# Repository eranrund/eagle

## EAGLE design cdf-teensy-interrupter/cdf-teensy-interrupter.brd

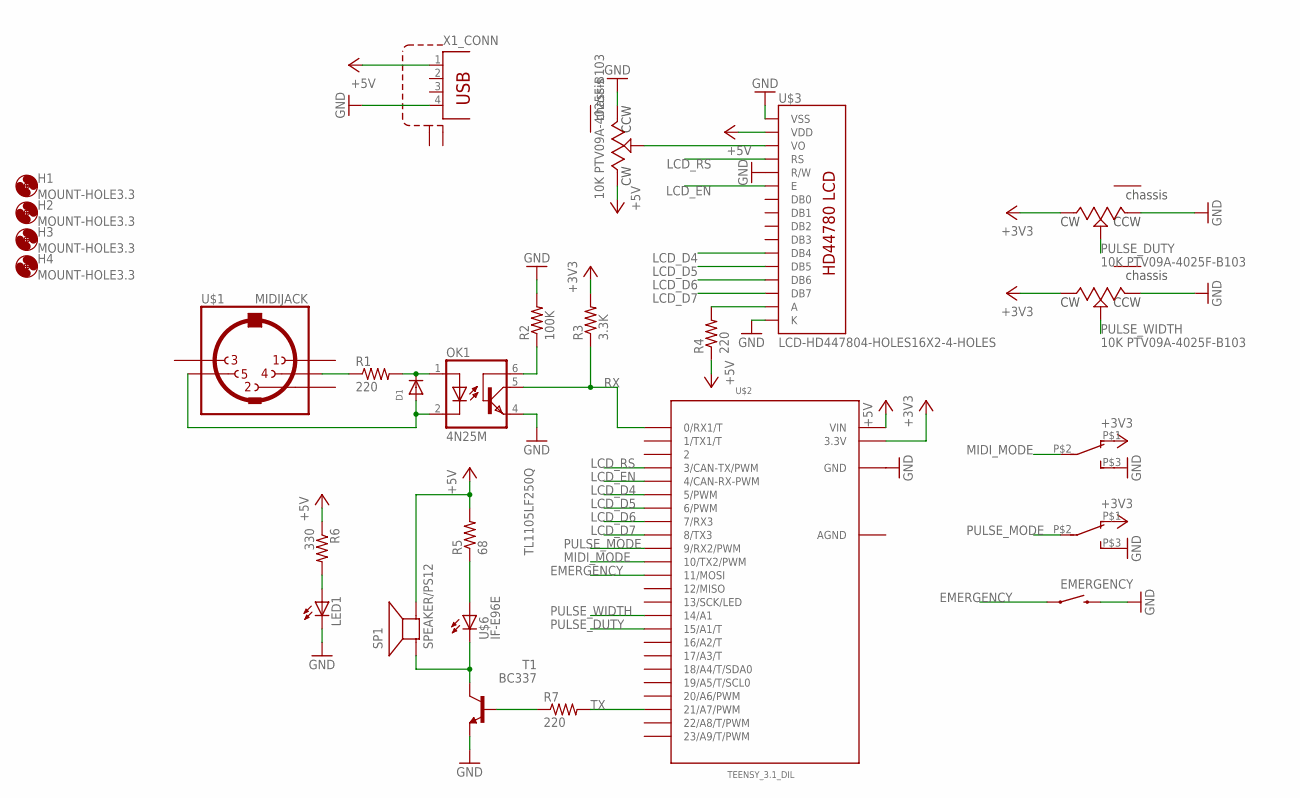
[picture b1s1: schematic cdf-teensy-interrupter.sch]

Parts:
D1: DIODEDO-1N4148; DO-1N4148
EMERGENCY: SWITCH-MOMENTARY-2PTH; TACTILE-PTH
H1, H2, H3, H4: MOUNT-HOLE3.3; 3,3
LCD_BL: 10K PTV09A-4025F-B103; PTV09A-4
LED1: LED5MM
MIDI_MODE: 100SP1T1B4M2QE
OK1: 4N25M; DIL06
PULSE_DUTY: 10K PTV09A-4025F-B103; PTV09A-4
PULSE_MODE: 100SP1T1B4M2QE
PULSE_WIDTH: 10K PTV09A-4025F-B103; PTV09A-4
R1, R4, R7: 220; 0204/7
R2: 100K; 0204/7
R3: 3.3K; 0204/7
R5: 68; 0204/7
R6: 330; 0204/7
SP1: SPEAKER/PS12; PS12
T1: BC337; TO92
U$1: MIDIJACK; CP-2350
U$2: TEENSY_3.1_DIL; TEENSY3-DIL
U$3: LCD-HD447804-HOLES16X2-4-HOLES; LCD-16X2-4HOLES
U$6: IF-E96E
X1: TE-292304-1

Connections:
+3V3: MIDI_MODE.P$1 (1), PULSE_DUTY.3 (CW), PULSE_MODE.P$1 (1), PULSE_WIDTH.3 (CW), R3.2, U$2.3.3V
+5V: LCD_BL.3 (CW), R4.1, R5.2, R6.1, SP1.P$2 (-), U$2.VIN, U$3.2 (VDD), X1.1
AGND: U$2.AGND
EMERGENCY: EMERGENCY.1, U$2.11 (11/MOSI)
GND: EMERGENCY.3 (2), LCD_BL.1 (CCW), LED1.K (C), MIDI_MODE.P$3 (3), OK1.4 (EMI), PULSE_DUTY.1 (CCW), PULSE_MODE.P$3 (3), PULSE_WIDTH.1 (CCW), R2.2, T1.1 (E), U$2.GND, U$3.1 (VSS), U$3.5 (R/W), U$3.16 (K), X1.4
LCD_D4: U$2.5 (5/PWM), U$3.11 (DB4)
LCD_D5: U$2.6 (6/PWM), U$3.12 (DB5)
LCD_D6: U$2.7 (7/RX3), U$3.13 (DB6)
LCD_D7: U$2.8 (8/TX3), U$3.14 (DB7)
LCD_EN: U$2.4 (4/CAN-RX-PWM), U$3.6 (E)
LCD_RS: U$2.3 (3/CAN-TX/PWM), U$3.4 (RS)
MIDI_MODE: MIDI_MODE.P$2 (2), U$2.10 (10/TX2/PWM)
unnamed: R1.1, U$1.4
unnamed: D1.C, OK1.1 (A), R1.2
unnamed: D1.A, OK1.2 (C), U$1.5
unnamed: OK1.6 (BAS), R2.1
unnamed: LCD_BL.2 (WIPER), U$3.3 (VO)
unnamed: R4.2, U$3.15 (A)
unnamed: R7.1, T1.2 (B)
unnamed: R5.1, U$6.P$2_ANODE+ (A)
unnamed: LED1.A, R6.2
unnamed: SP1.P$1 (+), T1.3 (C), U$6.P$1_CATHODE- (C)
PULSE_DUTY: PULSE_DUTY.2 (WIPER), U$2.15/A1 (15/A1/T)
PULSE_MODE: PULSE_MODE.P$2 (2), U$2.9 (9/RX2/PWM)
PULSE_WIDTH: PULSE_WIDTH.2 (WIPER), U$2.14/A0 (14/A1)
RX: OK1.5 (COL), R3.1, U$2.0 (0/RX1/T)
TX: R7.2, U$2.21/A7 (21/A7/PWM)

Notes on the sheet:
TL1105LF250Q

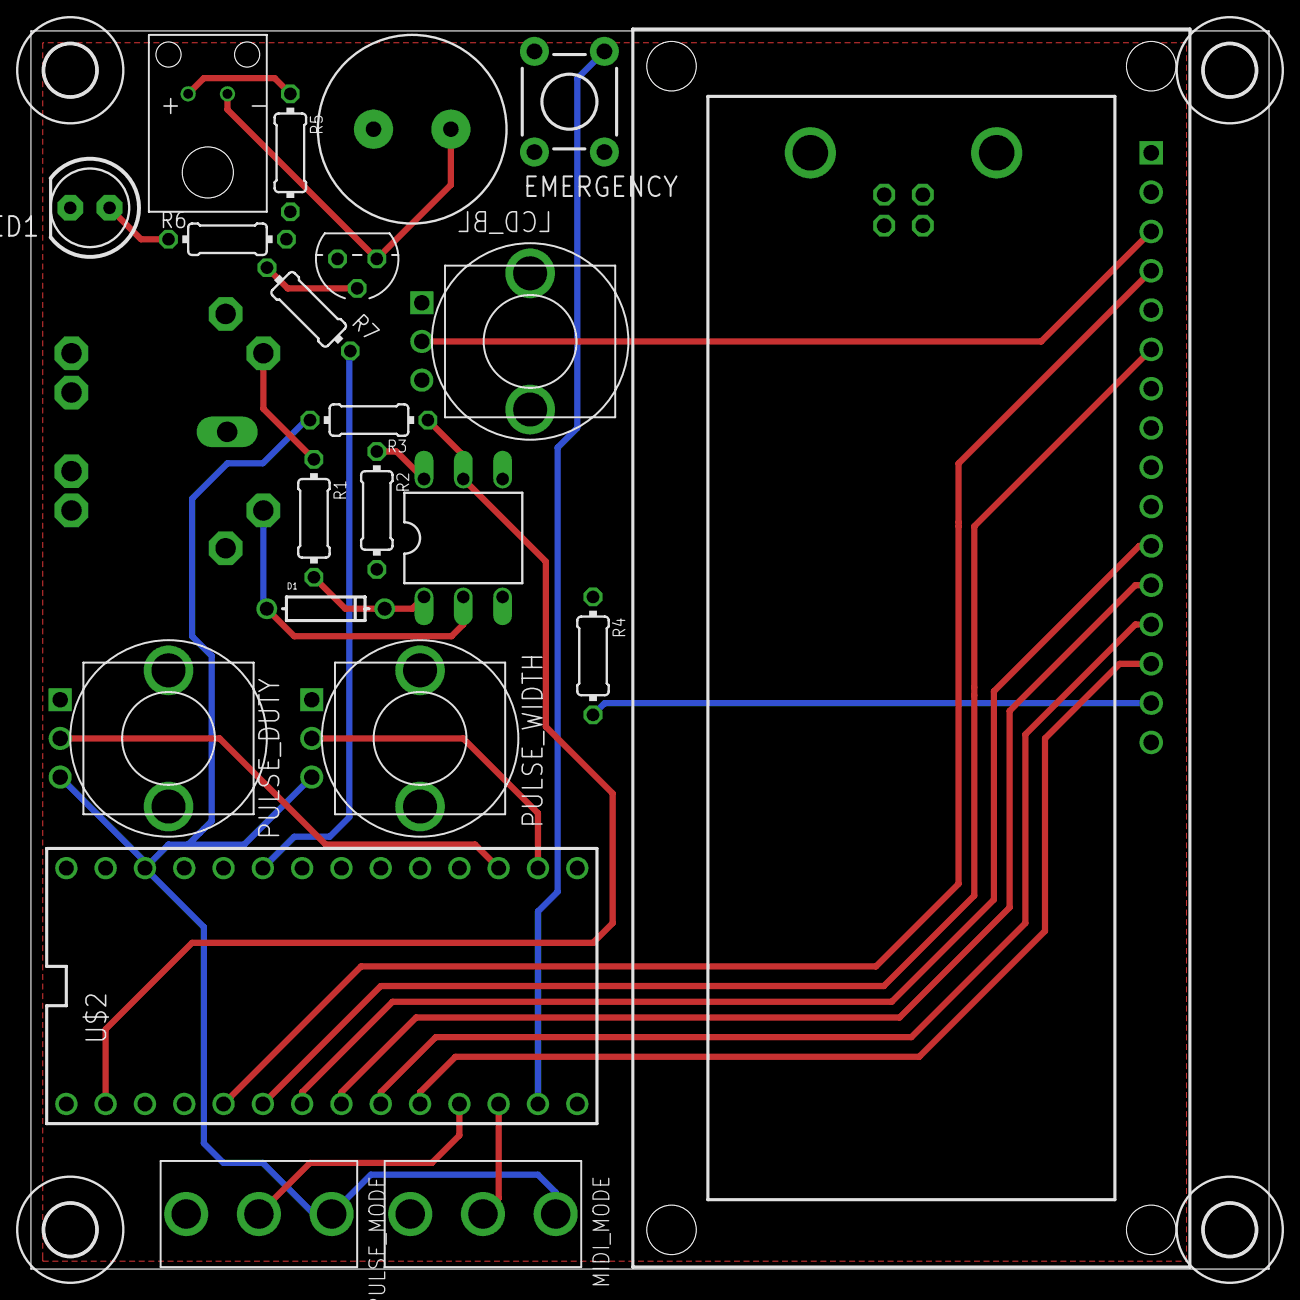
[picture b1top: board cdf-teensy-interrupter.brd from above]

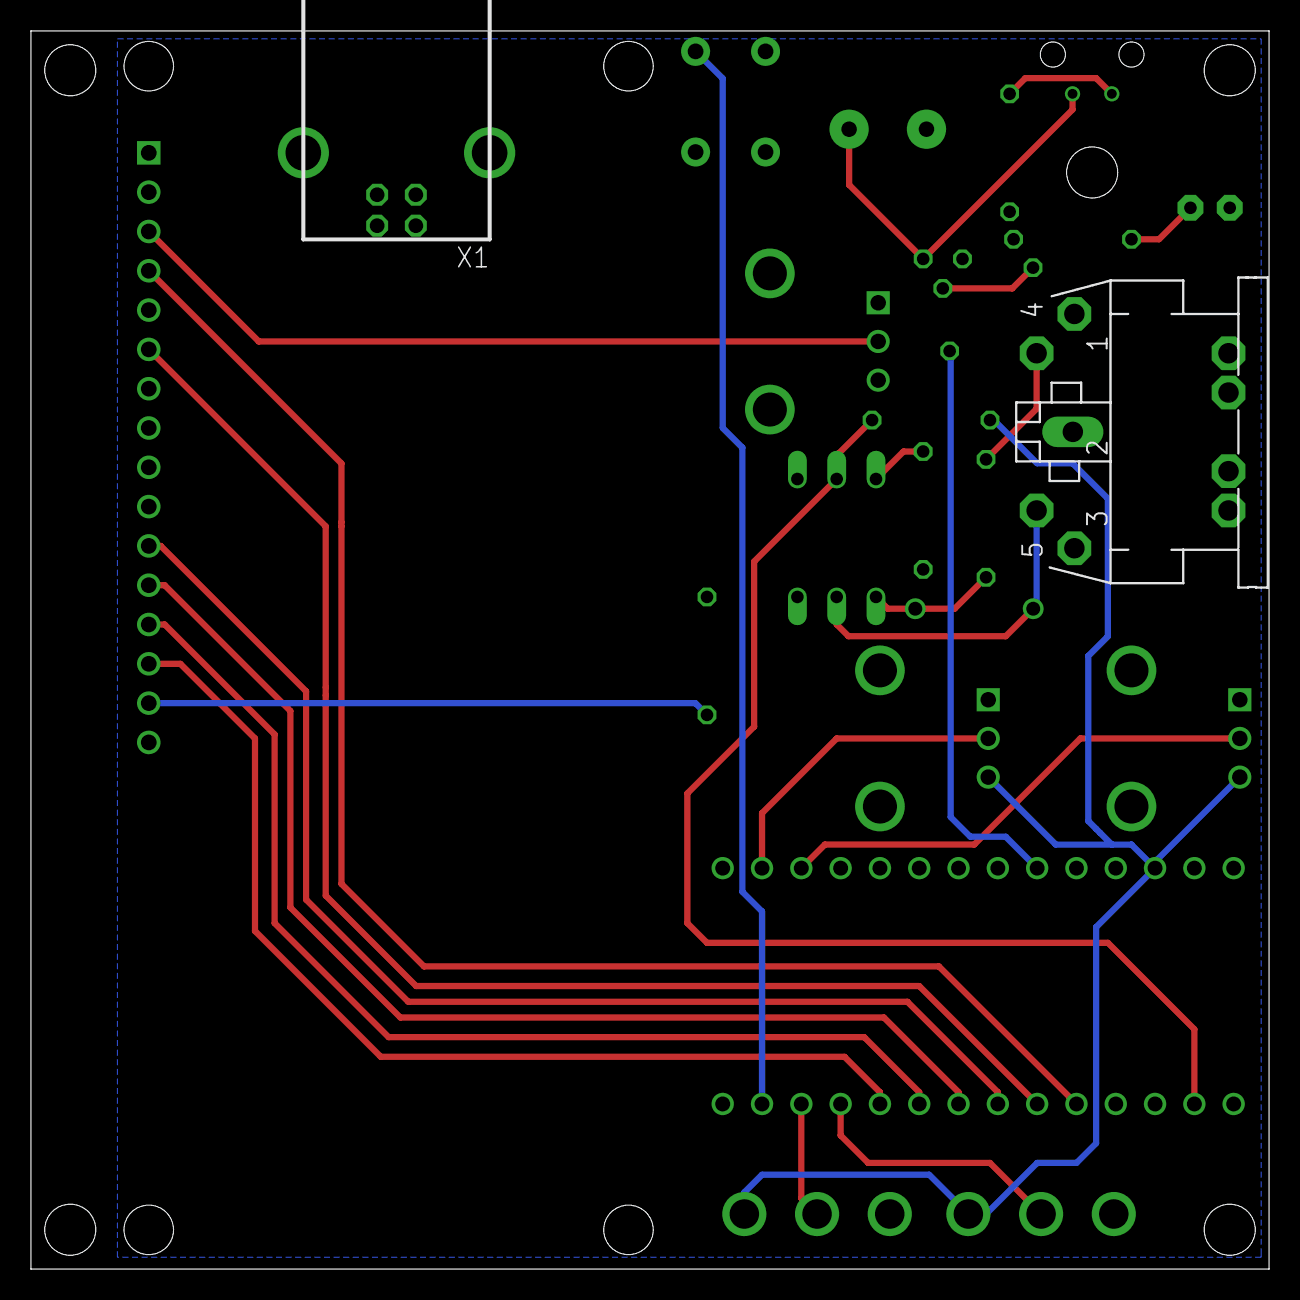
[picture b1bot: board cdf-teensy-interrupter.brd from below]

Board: 2 copper layers, 80.0 x 80.0 mm, 27 parts (2 on the bottom side), 26 nets.

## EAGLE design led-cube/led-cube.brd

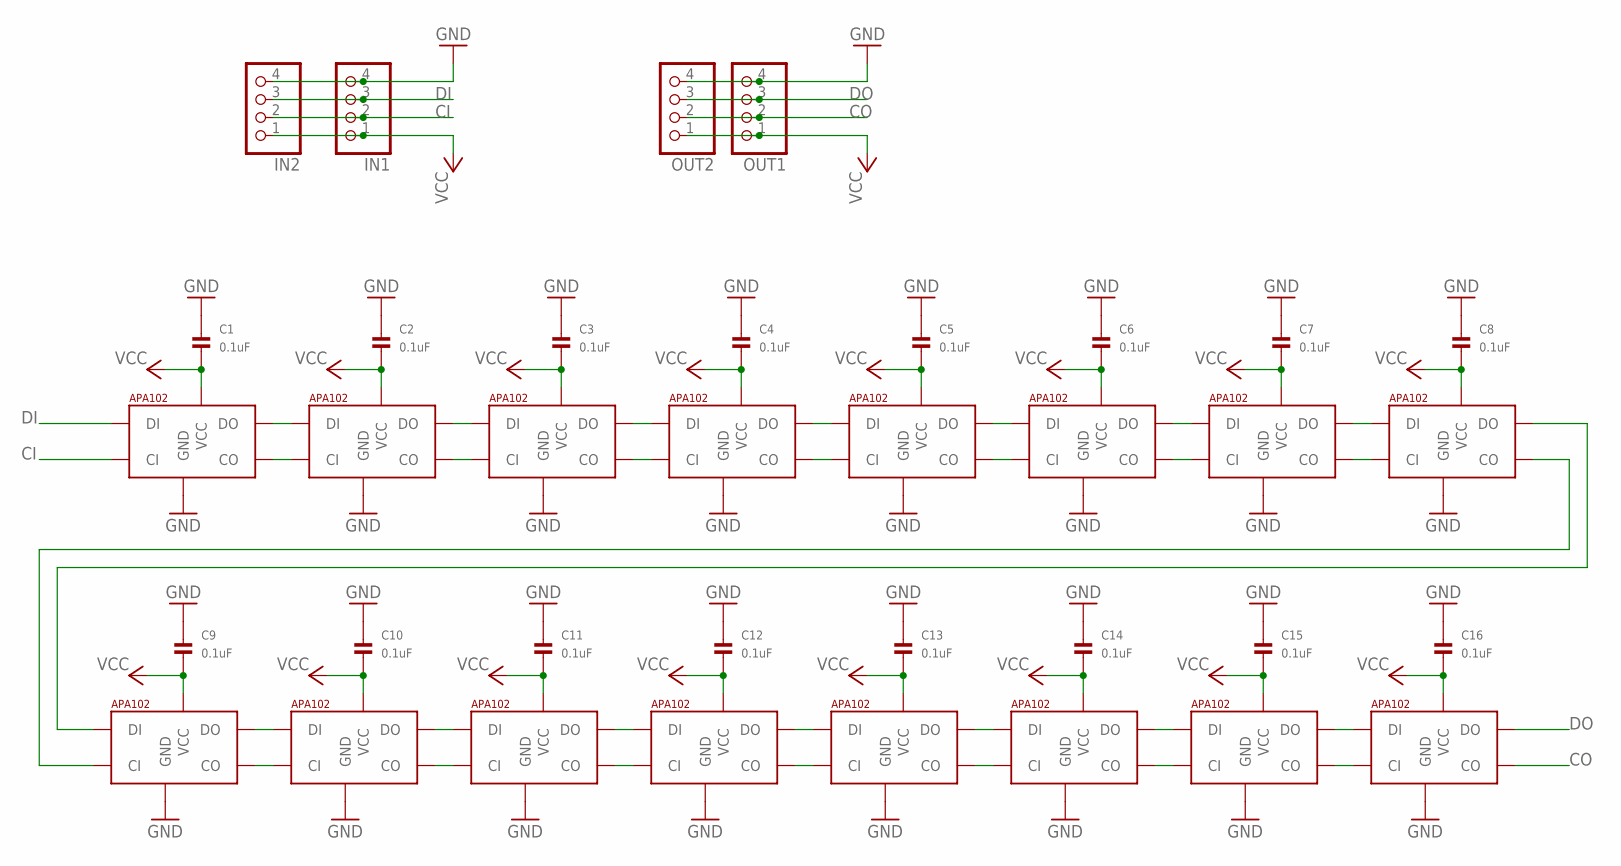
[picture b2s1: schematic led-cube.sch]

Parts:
C1, C2, C3, C4, C5, C6, C7, C8, C9, C10, C11, C12, C13, C14, C15, C16: 0.1uF; 0603
IN1, IN2: PINHD-1X4; 1X04
OUT1, OUT2: PINHD-1X4; 1X04
U$1, U$2, U$3, U$4, U$5, U$6, U$7, U$8, U$9, U$10, U$11, U$12, U$13, U$14, U$15, U$16: APA1025050; APA102_5050

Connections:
CI: IN1.2, IN2.2, U$1.5 (CI)
CO: OUT1.2, OUT2.2, U$16.2 (CO)
DI: IN1.3, IN2.3, U$1.4 (DI)
DO: OUT1.3, OUT2.3, U$16.3 (DO)
GND: C1.1, C2.1, C3.1, C4.1, C5.1, C6.1, C7.1, C8.1, C9.1, C10.1, C11.1, C12.1, C13.1, C14.1, C15.1, C16.1, IN1.4, IN2.4, OUT1.4, OUT2.4, U$1.6 (GND), U$2.6 (GND), U$3.6 (GND), U$4.6 (GND), U$5.6 (GND), U$6.6 (GND), U$7.6 (GND), U$8.6 (GND), U$9.6 (GND), U$10.6 (GND), U$11.6 (GND), U$12.6 (GND), U$13.6 (GND), U$14.6 (GND), U$15.6 (GND), U$16.6 (GND)
unnamed: U$1.2 (CO), U$2.5 (CI)
unnamed: U$1.3 (DO), U$2.4 (DI)
unnamed: U$3.2 (CO), U$4.5 (CI)
unnamed: U$3.3 (DO), U$4.4 (DI)
unnamed: U$2.3 (DO), U$3.4 (DI)
unnamed: U$2.2 (CO), U$3.5 (CI)
unnamed: U$5.2 (CO), U$6.5 (CI)
unnamed: U$5.3 (DO), U$6.4 (DI)
unnamed: U$7.2 (CO), U$8.5 (CI)
unnamed: U$7.3 (DO), U$8.4 (DI)
unnamed: U$6.3 (DO), U$7.4 (DI)
unnamed: U$6.2 (CO), U$7.5 (CI)
unnamed: U$4.3 (DO), U$5.4 (DI)
unnamed: U$4.2 (CO), U$5.5 (CI)
unnamed: U$9.2 (CO), U$10.5 (CI)
unnamed: U$9.3 (DO), U$10.4 (DI)
unnamed: U$11.2 (CO), U$12.5 (CI)
unnamed: U$11.3 (DO), U$12.4 (DI)
unnamed: U$10.3 (DO), U$11.4 (DI)
unnamed: U$10.2 (CO), U$11.5 (CI)
unnamed: U$13.2 (CO), U$14.5 (CI)
unnamed: U$13.3 (DO), U$14.4 (DI)
unnamed: U$15.2 (CO), U$16.5 (CI)
unnamed: U$15.3 (DO), U$16.4 (DI)
unnamed: U$14.3 (DO), U$15.4 (DI)
unnamed: U$14.2 (CO), U$15.5 (CI)
unnamed: U$12.3 (DO), U$13.4 (DI)
unnamed: U$12.2 (CO), U$13.5 (CI)
unnamed: U$8.3 (DO), U$9.4 (DI)
unnamed: U$8.2 (CO), U$9.5 (CI)
VCC: C1.2, C2.2, C3.2, C4.2, C5.2, C6.2, C7.2, C8.2, C9.2, C10.2, C11.2, C12.2, C13.2, C14.2, C15.2, C16.2, IN1.1, IN2.1, OUT1.1, OUT2.1, U$1.1 (VCC), U$2.1 (VCC), U$3.1 (VCC), U$4.1 (VCC), U$5.1 (VCC), U$6.1 (VCC), U$7.1 (VCC), U$8.1 (VCC), U$9.1 (VCC), U$10.1 (VCC), U$11.1 (VCC), U$12.1 (VCC), U$13.1 (VCC), U$14.1 (VCC), U$15.1 (VCC), U$16.1 (VCC)

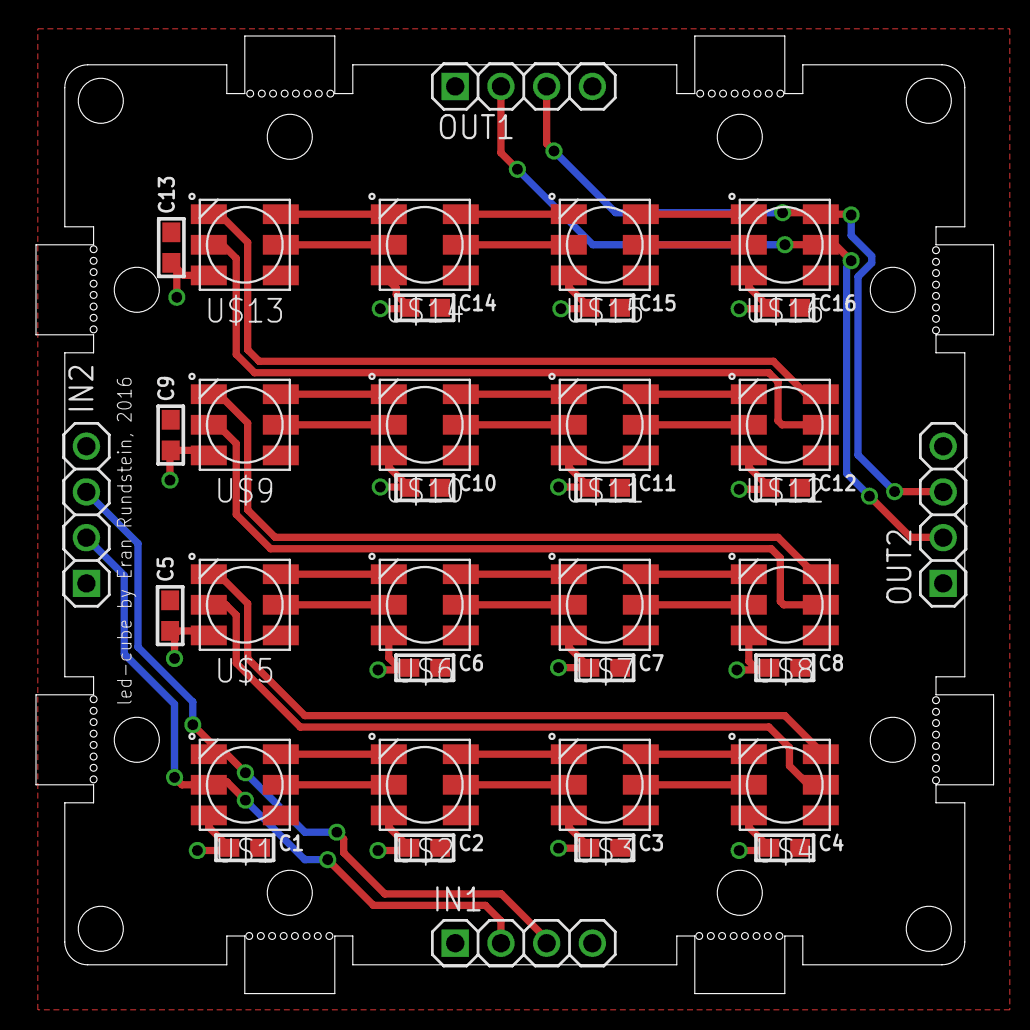
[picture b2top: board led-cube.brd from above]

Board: 2 copper layers, 53.2 x 53.2 mm, 36 parts (0 on the bottom side), 36 nets.

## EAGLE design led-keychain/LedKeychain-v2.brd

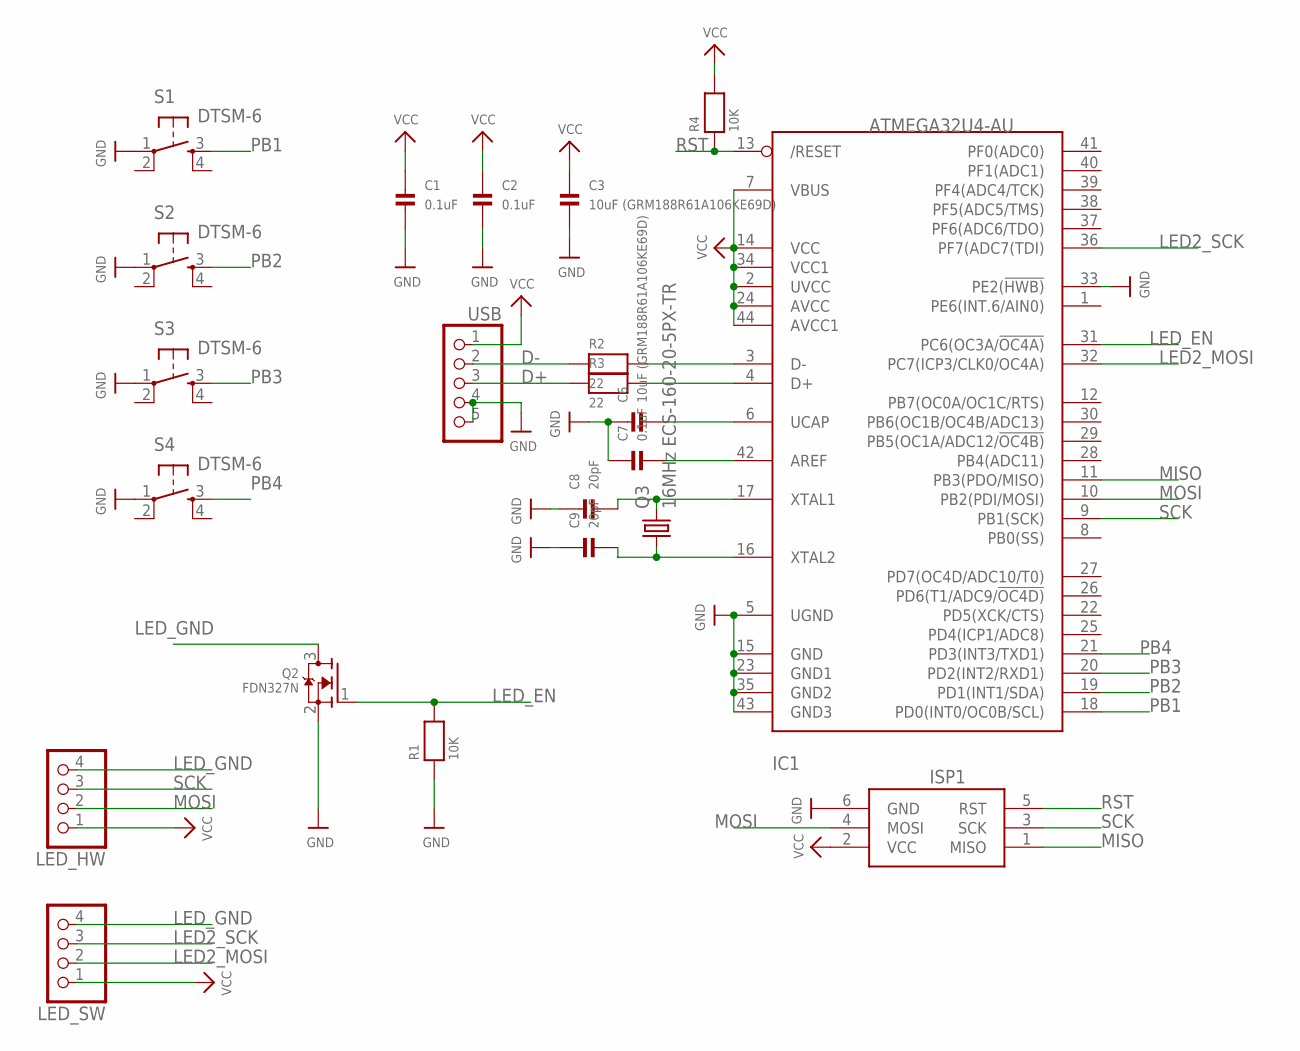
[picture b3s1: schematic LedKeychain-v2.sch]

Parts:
C1, C2, C7: 0.1uF; 0603-MINI
C3, C6: 10uF (GRM188R61A106KE69D); 1206
C8, C9: 20pF; 0603-MINI
IC1: ATMEGA32U4-AU; TQFP44
ISP1: AVRISP-6; AVRISP
LED_HW: HEADER-1X4ROUND; 1X04_ROUND
LED_SW: HEADER-1X4ROUND; 1X04_ROUND
Q2: FDN327N; SOT23-WIDE
Q3: 16MHz ECS-160-20-5PX-TR; HC49UP
R1, R4: 10K; 0603-MINI
R2, R3: 22; 0603-MINI
S1, S2, S3, S4: DTSM-6
USB: PINHD-1X5/90; 1X05/90

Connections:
D+: R3.1, USB.3
D-: R2.1, USB.2
GND: C1.2, C2.2, C3.2, C6.1, C7.1, C8.1, C9.1, IC1.5 (UGND), IC1.15 (GND), IC1.23 (GND1), IC1.33 (PE2(!HWB)), IC1.35 (GND2), IC1.43 (GND3), ISP1.6 (GND), Q2.2 (S), R1.1, S1.1, S2.1, S3.1, S4.1, USB.4, USB.5
LED2_MOSI: IC1.32 (PC7(ICP3/CLK0/OC4A)), LED_SW.2
LED2_SCK: IC1.36 (PF7(ADC7(TDI)), LED_SW.3
LED_EN: IC1.31 (PC6(OC3A/!OC4A)), Q2.1 (G), R1.2
LED_GND: LED_HW.4, LED_SW.4, Q2.3 (D)
MISO: IC1.11 (PB3(PDO/MISO)), ISP1.1 (MISO)
MOSI: IC1.10 (PB2(PDI/MOSI)), ISP1.4 (MOSI), LED_HW.2
unnamed: IC1.3 (D-), R2.2
unnamed: IC1.4 (D+), R3.2
unnamed: C6.2, IC1.6 (UCAP)
unnamed: C7.2, IC1.42 (AREF)
unnamed: C9.2, IC1.16 (XTAL2), Q3.1
unnamed: C8.2, IC1.17 (XTAL1), Q3.2
PB1: IC1.18 (PD0(INT0/OC0B/SCL)), S1.3
PB2: IC1.19 (PD1(INT1/SDA)), S2.3
PB3: IC1.20 (PD2(INT2/RXD1)), S3.3
PB4: IC1.21 (PD3(INT3/TXD1)), S4.3
RST: IC1.13 (/RESET), ISP1.5 (RST), R4.1
SCK: IC1.9 (PB1(SCK)), ISP1.3 (SCK), LED_HW.3
VCC: C1.1, C2.1, C3.1, IC1.2 (UVCC), IC1.7 (VBUS), IC1.14 (VCC), IC1.24 (AVCC), IC1.34 (VCC1), IC1.44 (AVCC1), ISP1.2 (VCC), LED_HW.1, LED_SW.1, R4.2, USB.1

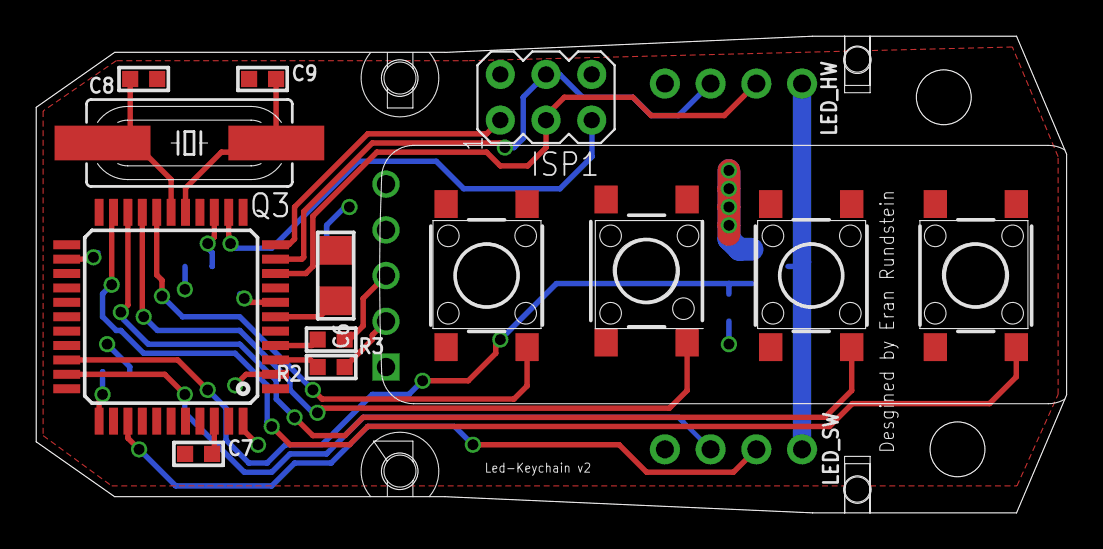
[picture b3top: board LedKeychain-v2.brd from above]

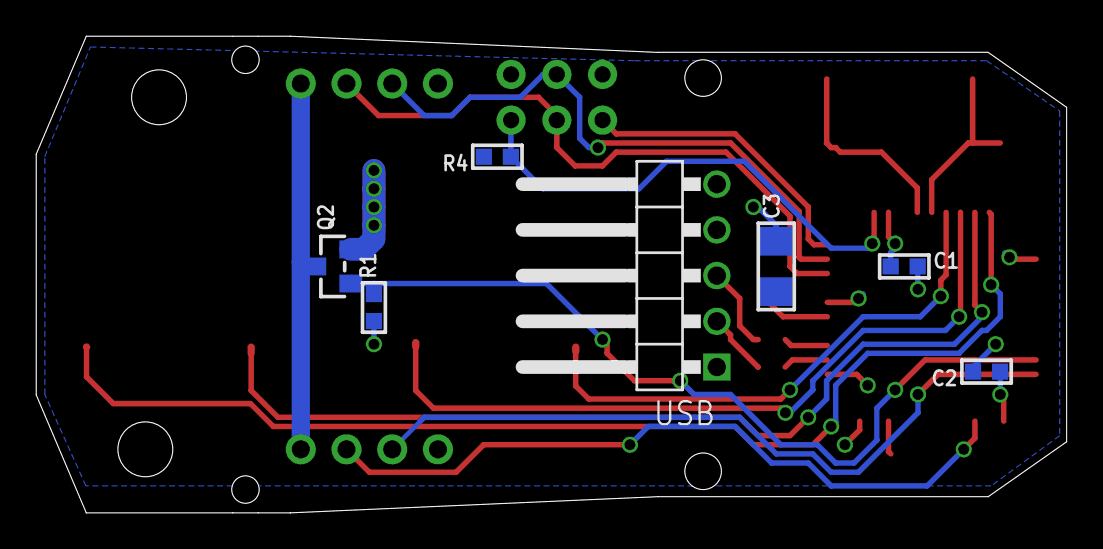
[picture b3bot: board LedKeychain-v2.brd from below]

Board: 2 copper layers, 57.2 x 26.5 mm, 22 parts (7 on the bottom side), 22 nets.

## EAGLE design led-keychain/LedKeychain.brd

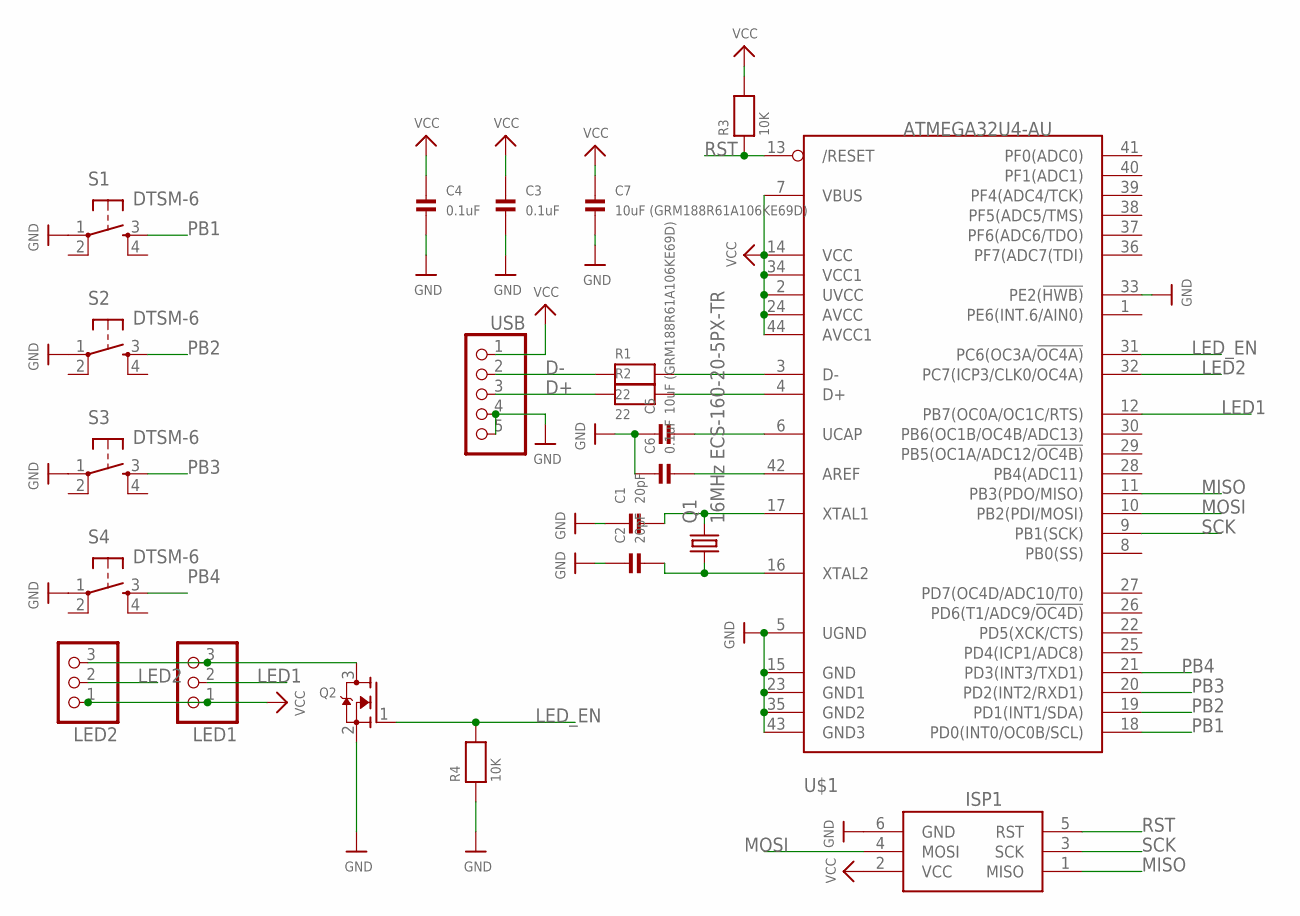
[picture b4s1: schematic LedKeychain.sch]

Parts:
C1, C2: 20pF; 0603-MINI
C3, C4, C6: 0.1uF; 0603-MINI
C5, C7: 10uF (GRM188R61A106KE69D); 0603-MINI
ISP1: AVRISP-6; AVRISP
LED1, LED2: PINHD-1X3; 1X03
Q1: 16MHz ECS-160-20-5PX-TR; HC49UP
Q2: MOSFET-NWIDE; SOT23-WIDE
R1, R2: 22; 0603-MINI
R3, R4: 10K; 0603-MINI
S1, S2, S3, S4: DTSM-6
U$1: ATMEGA32U4-AU; TQFP44
USB: PINHD-1X5/90; 1X05/90

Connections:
D+: R2.1, USB.3
D-: R1.1, USB.2
GND: C1.1, C2.1, C3.2, C4.2, C5.1, C6.1, C7.2, ISP1.6 (GND), Q2.2 (S), R4.1, S1.1, S2.1, S3.1, S4.1, U$1.5 (UGND), U$1.15 (GND), U$1.23 (GND1), U$1.33 (PE2(!HWB)), U$1.35 (GND2), U$1.43 (GND3), USB.4, USB.5
LED1: LED1.2, U$1.12 (PB7(OC0A/OC1C/RTS))
LED2: LED2.2, U$1.32 (PC7(ICP3/CLK0/OC4A))
LED_EN: Q2.1 (G), R4.2, U$1.31 (PC6(OC3A/!OC4A))
MISO: ISP1.1 (MISO), U$1.11 (PB3(PDO/MISO))
MOSI: ISP1.4 (MOSI), U$1.10 (PB2(PDI/MOSI))
unnamed: C2.2, Q1.1, U$1.16 (XTAL2)
unnamed: C1.2, Q1.2, U$1.17 (XTAL1)
unnamed: R1.2, U$1.3 (D-)
unnamed: R2.2, U$1.4 (D+)
unnamed: C5.2, U$1.6 (UCAP)
unnamed: C6.2, U$1.42 (AREF)
unnamed: LED1.3, LED2.3, Q2.3 (D)
PB1: S1.3, U$1.18 (PD0(INT0/OC0B/SCL))
PB2: S2.3, U$1.19 (PD1(INT1/SDA))
PB3: S3.3, U$1.20 (PD2(INT2/RXD1))
PB4: S4.3, U$1.21 (PD3(INT3/TXD1))
RST: ISP1.5 (RST), R3.1, U$1.13 (/RESET)
SCK: ISP1.3 (SCK), U$1.9 (PB1(SCK))
VCC: C3.1, C4.1, C7.1, ISP1.2 (VCC), LED1.1, LED2.1, R3.2, U$1.2 (UVCC), U$1.7 (VBUS), U$1.14 (VCC), U$1.24 (AVCC), U$1.34 (VCC1), U$1.44 (AVCC1), USB.1

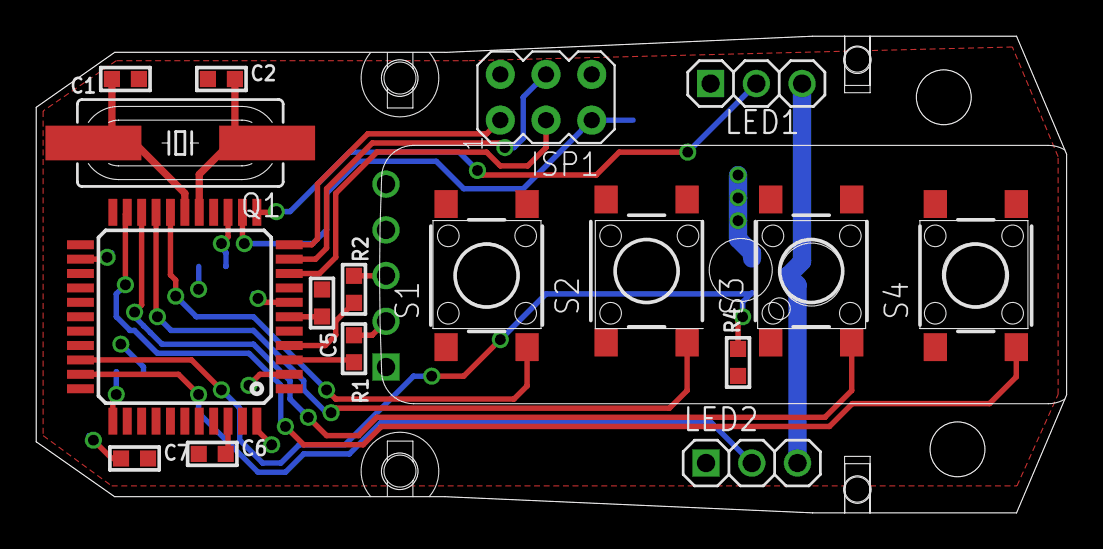
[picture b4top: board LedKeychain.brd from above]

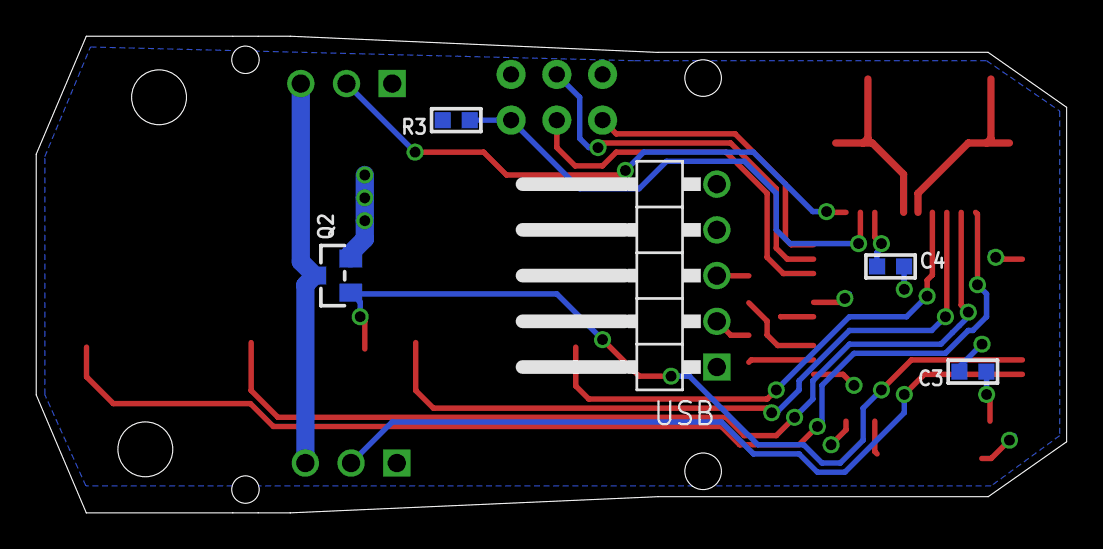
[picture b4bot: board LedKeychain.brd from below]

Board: 2 copper layers, 57.2 x 26.5 mm, 22 parts (5 on the bottom side), 22 nets.

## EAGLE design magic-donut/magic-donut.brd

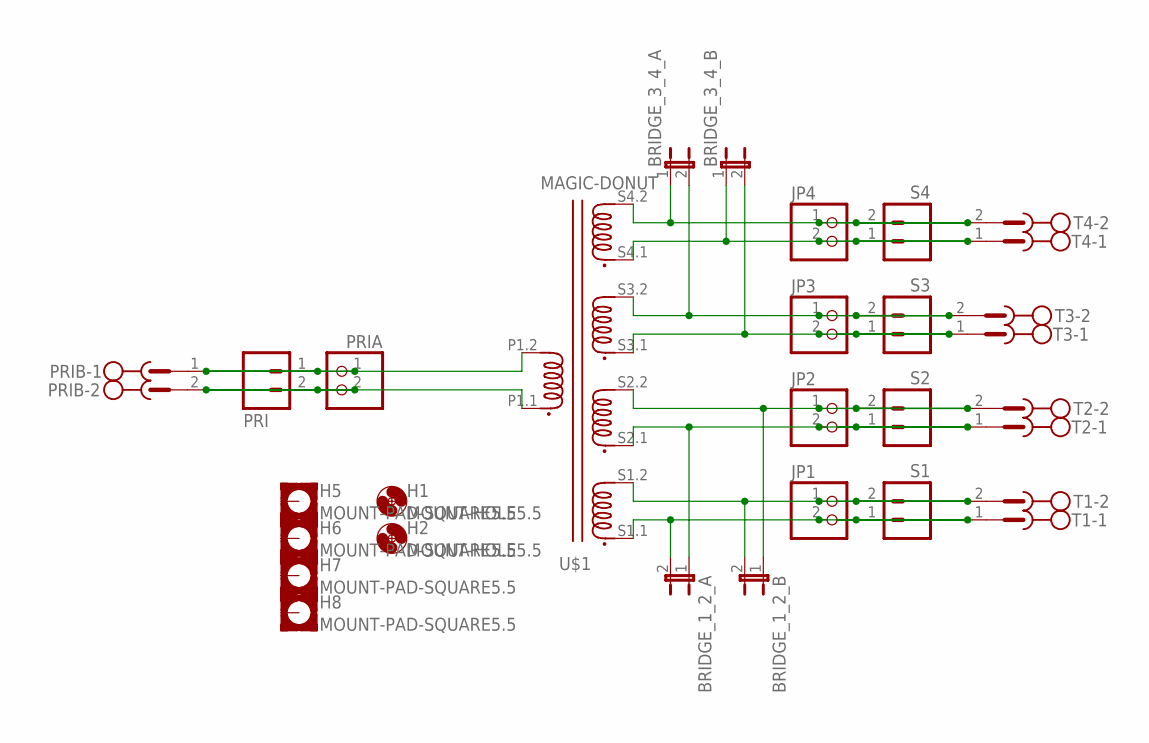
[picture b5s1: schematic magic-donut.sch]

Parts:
BRIDGE_1_2_A, BRIDGE_1_2_B, BRIDGE_3_4_A, BRIDGE_3_4_B: JP1E; JP1
H1, H2: MOUNT-HOLE5.5; 5,5
H5, H6, H7, H8: MOUNT-PAD-SQUARE5.5; 5,5-PAD-SQUARE
JP1, JP2, JP3, JP4: PINHD-1X2; 1X02
PRI: M02JST-PTH-2; JST-2-PTH
PRIA: PINHD-1X2; 1X02
PRIB: MSTBV2
S1, S2, S3, S4: M02JST-PTH-2; JST-2-PTH
T1, T2, T3, T4: MSTBV2
U$1: MAGIC-DONUT; TOROID

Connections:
unnamed: BRIDGE_1_2_A.2, JP1.2, S1.1, T1.1, U$1.S1.1
unnamed: BRIDGE_1_2_A.1, JP2.2, S2.1, T2.1, U$1.S2.1
unnamed: BRIDGE_3_4_A.1, JP4.1, S4.2, T4.2, U$1.S4.2
unnamed: BRIDGE_3_4_B.1, JP4.2, S4.1, T4.1, U$1.S4.1
unnamed: BRIDGE_3_4_A.2, JP3.1, S3.2, T3.2, U$1.S3.2
unnamed: BRIDGE_3_4_B.2, JP3.2, S3.1, T3.1, U$1.S3.1
unnamed: BRIDGE_1_2_B.1, JP2.1, S2.2, T2.2, U$1.S2.2
unnamed: BRIDGE_1_2_B.2, JP1.1, S1.2, T1.2, U$1.S1.2
unnamed: PRI.1, PRIA.1, PRIB.1, U$1.P1.2
unnamed: PRI.2, PRIA.2, PRIB.2, U$1.P1.1

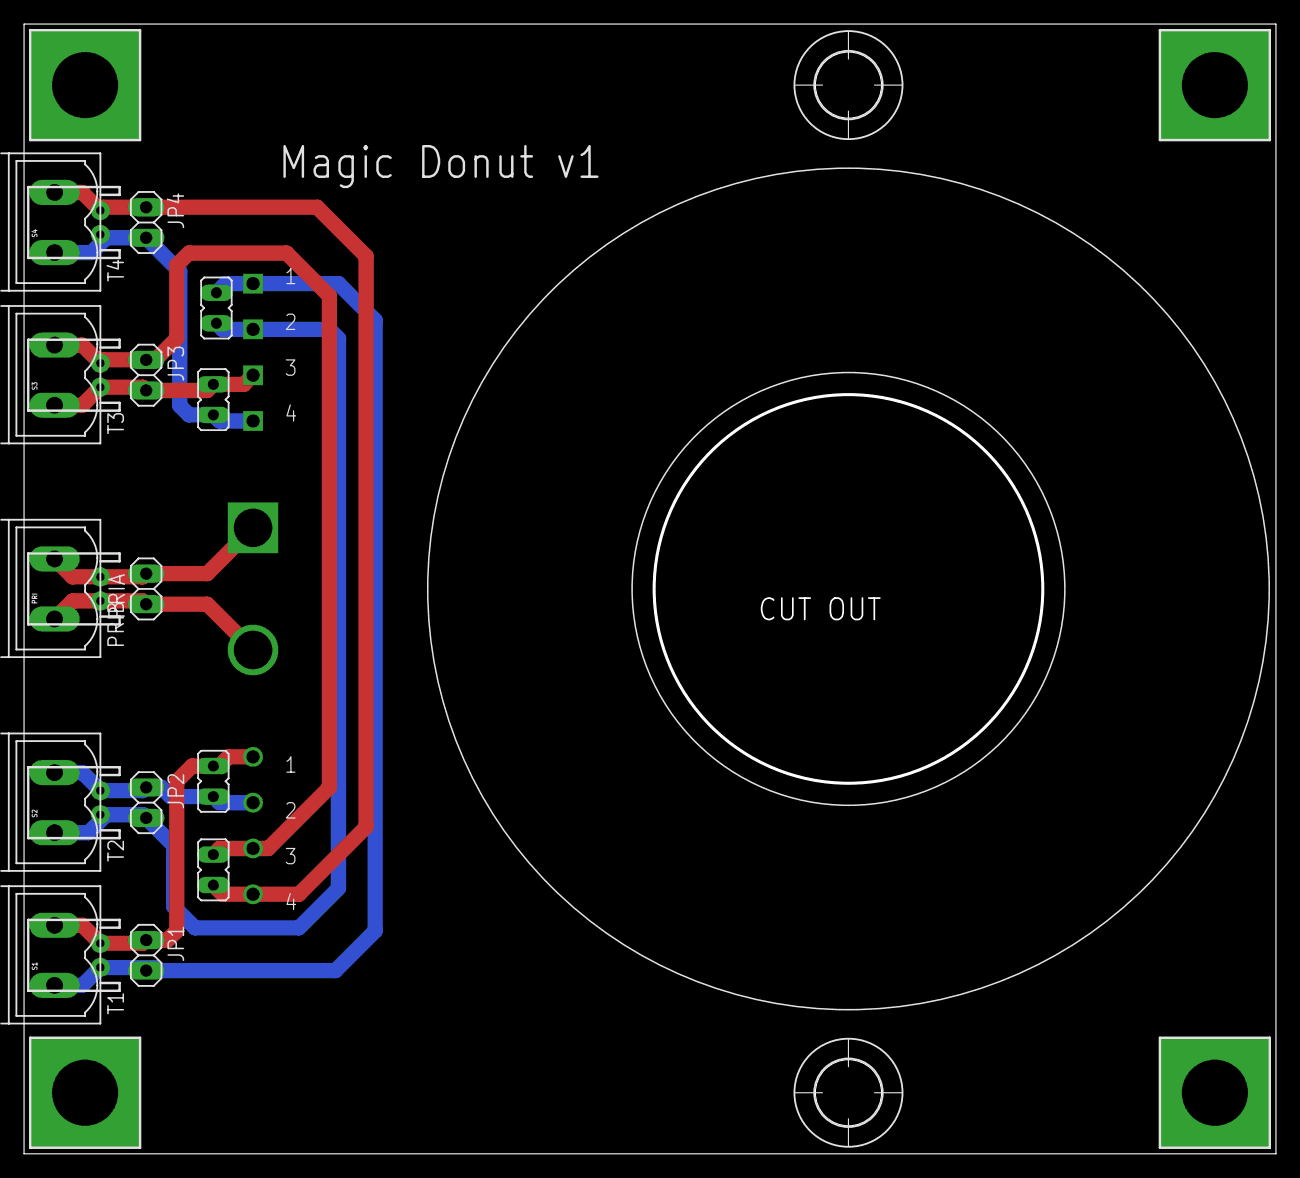
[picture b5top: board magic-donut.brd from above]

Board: 2 copper layers, 104.1 x 94.0 mm, 26 parts (0 on the bottom side), 10 nets.

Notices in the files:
parts and their libraries:
SparkFun-Electromechanical: Licensing: Creative Commons ShareAlike 4.0 International - https://creativecommons.org/licenses/by-sa/4.0
microbuilder: This work is placed in the public domain, and may be freely used for commercial and non-commercial work with the following conditions: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
